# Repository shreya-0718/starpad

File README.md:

# starpad 🌠
a cute diy macropad!

link to my journal.md: [starpad - journal](JOURNAL.md)

## What is starpad?
Starpad is my DIY macropad! It has 8 buttons, a rotary encoder, and an OLED display. It can control volume, play/pause media, and more! I named it starpad because I wanted to silkscreen stars onto it :)

## Why did I make starpad?
I made starpad for hackpad, and to have a cute + functional macropad. I wanted to learn more about electronics and PCB design on KiCad. (I also used Fusion 360 for the custom case!)

## How did I make starpad?
I made starpad by first designing the schematic in KiCad, then routing the PCB and adding silkscreen art. I designed the case in Fusion 360, procrastinated, and wrote the firmware using kmk.

## Learnings and struggles 🌱
While I'm pretty familiar with KiCad now, I learned about connecting the backlighting LEDs, and how to use a rotary encoder and OLED. This was my first time using kmk, so I learned how to use that to write firmware using the KMK Documentation.

## Images 
Here are some images of starpad:

## Bill of Materials (BOM)
Here is the list of physical materials for starpad:

- 1x Seeed Studio XIAO RP2040
- 1x 0.91" OLED Display
- 8x Cherry MX Switches
- 8x DSA Keycaps
- 1x EC11 Rotary Encoder
- 9x 1N4148 Diodes
- 9x SK6812 MINI-E LEDs
- 4x M3x16mm Screws
- 4x M3x5mm Heatset Inserts
- 1x 3D-printed knob for the rotary encoder
- 1x 3D-printed case (with 2 pieces)

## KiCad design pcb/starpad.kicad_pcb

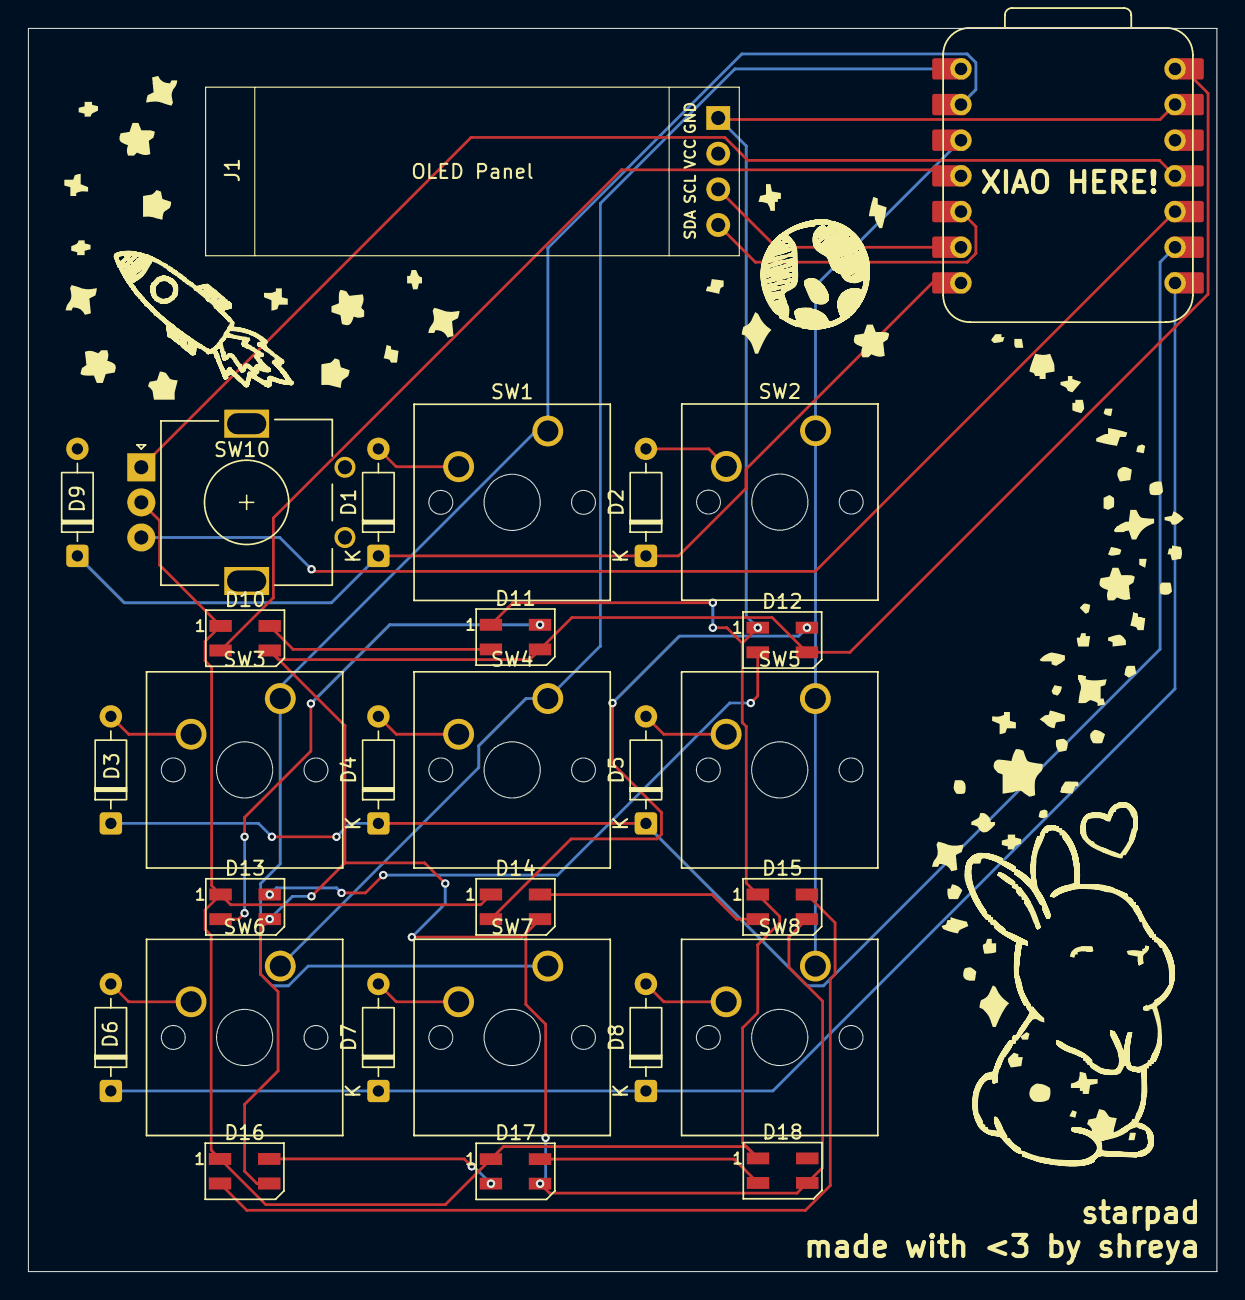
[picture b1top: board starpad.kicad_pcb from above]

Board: 2 copper layers, 84.6 x 88.5 mm, 29 parts (0 on the bottom side), 29 nets.

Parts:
D1, D2, D3, D4, D5, D6, D7, D8, D9: 1N4148; D_DO-35_SOD27_P7.62mm_Horizontal
D10, D11, D12, D13, D14, D15, D16, D17, D18: SK6812; LED_SK6812MINI_PLCC4_3.5x3.5mm_P1.75mm
J1: OLED - Conn_01x04; SSD1306-0.91-OLED-4pin-128x32
SW1, SW2, SW3, SW4, SW5, SW6, SW7, SW8: SW_Push_45deg; SW_Cherry_MX_1.00u_PCB
SW10: RotaryEncoder_Switch; RotaryEncoder_Alps_EC11E_Vertical_H20mm
U1: XIAO-RP2040-DIP

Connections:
+5V: D10.3 (VDD), D11.3 (VDD), D12.3 (VDD), D13.3 (VDD), D14.3 (VDD), D15.3 (VDD), D16.3 (VDD), D17.3 (VDD), D18.3 (VDD), U1.14 (VBUS)
Col1: SW4.1, SW6.1, U1.1 (GPIO26/ADC0/A0)
Col2: SW1.1, SW3.1, SW7.1, U1.2 (GPIO27/ADC1/A1)
Col3: SW2.1, SW5.1, SW8.1, U1.3 (GPIO28/ADC2/A2)
GND: D10.1 (VSS), D11.1 (VSS), D12.1 (VSS), D13.1 (VSS), D14.1 (VSS), D15.1 (VSS), D16.1 (VSS), D17.1 (VSS), D18.1 (VSS), J1.1, SW10.C, U1.13 (GND)
LEDs: D10.2 (DIN), U1.4 (GPIO29/ADC3/A3)
unnamed: D1.2 (A), SW1.2
unnamed: D2.2 (A), SW2.2
unnamed: D3.2 (A), SW3.2
unnamed: D4.2 (A), SW4.2
unnamed: D5.2 (A), SW5.2
unnamed: D6.2 (A), SW6.2
unnamed: D7.2 (A), SW7.2
unnamed: D8.2 (A), SW8.2
unnamed: D10.4 (DOUT), D11.2 (DIN)
unnamed: D11.4 (DOUT), D13.2 (DIN)
unnamed: D12.2 (DIN), D13.4 (DOUT)
unnamed: D12.4 (DOUT), D14.2 (DIN)
unnamed: D14.4 (DOUT), D15.2 (DIN)
unnamed: D15.4 (DOUT), D16.2 (DIN)
unnamed: D16.4 (DOUT), D17.2 (DIN)
unnamed: D17.4 (DOUT), D18.2 (DIN)
Rota1: SW10.A, U1.11 (GPIO3/MOSI)
Rota2: SW10.B, U1.10 (GPIO4/MISO)
Row1: D1.1 (K), D2.1 (K), D9.1 (K), U1.7 (GPIO0/TX)
Row2: D3.1 (K), D4.1 (K), D5.1 (K), U1.9 (GPIO2/SCK)
Row3: D6.1 (K), D7.1 (K), D8.1 (K), U1.8 (GPIO1/RX)
SCL: J1.3, U1.6 (GPIO7/SCL)
SDA: J1.4, U1.5 (GPIO6/SDA)

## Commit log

2025-07-03 Added schematic.png
2025-07-05 Added PCB image
2025-07-05 Updated JOURNAL.md, added CAD images
2025-07-06 Added KMK
2025-07-06 Updated JOURNAL.md and README.md
2025-07-06 Added images and updated README.md
2025-07-06 Updated PCB
